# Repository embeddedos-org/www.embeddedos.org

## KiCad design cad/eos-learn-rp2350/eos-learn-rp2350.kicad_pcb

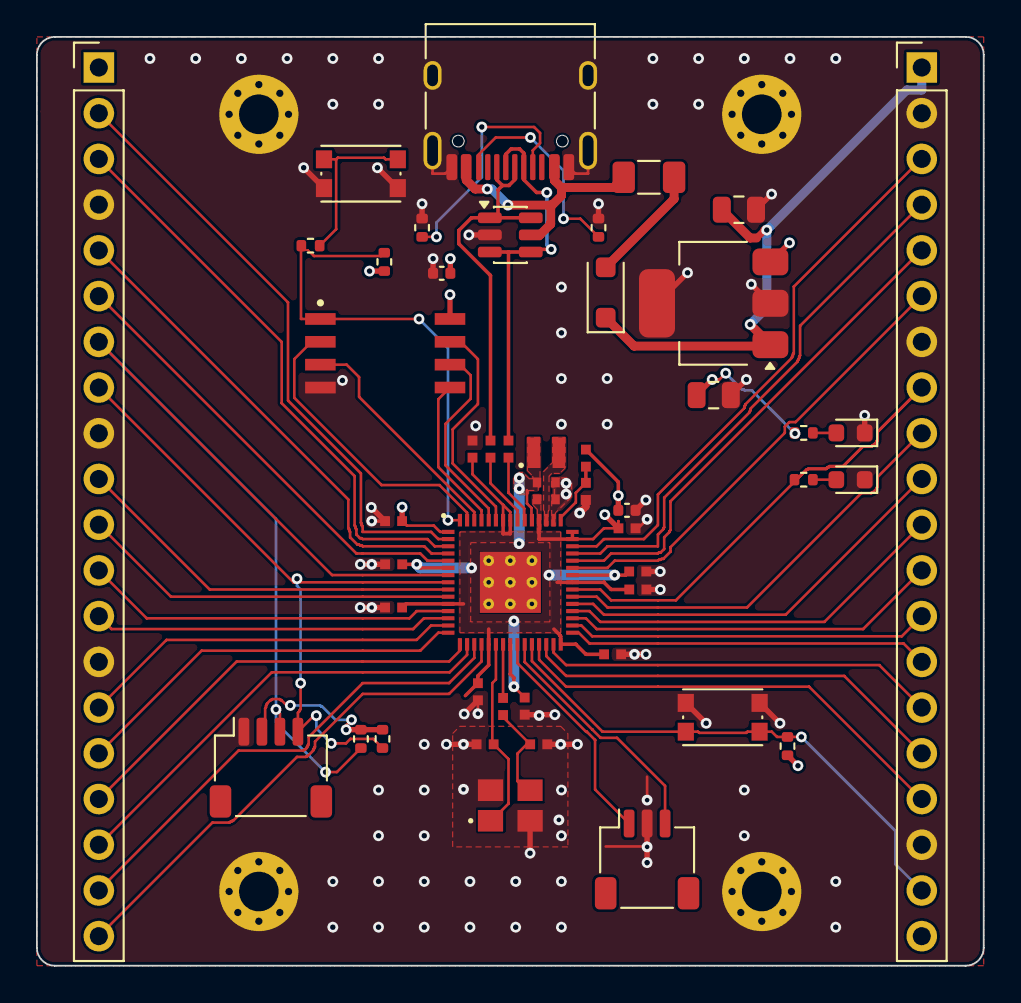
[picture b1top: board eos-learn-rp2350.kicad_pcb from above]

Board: 4 copper layers, 52.6 x 51.6 mm, 53 parts (0 on the bottom side), 59 nets.

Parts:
C1, C2: 10u; C_0805_2012Metric
C3, C4: 15p; generic_capc1005x50
C6, C7: 4.7u; generic_capc1005x50_wide
C9: 4.7u; generic_capc1005x50
C10, C11, C12, C13, C14, C15, C16, C18, C19, C20: 100n; generic_capc1005x50
C17, C21: 100n; C_0402_1005Metric
D1: MBR120VLSFT1G; D_SOD-123F
D2: PWR; LED_0603_1608Metric
D3: GP25; LED_0603_1608Metric
F1: 500mA; Fuse_1206_3216Metric
H1, H2, H3, H4: M2; MountingHole_2.2mm_M2_Pad_Via
J1: USB-C; USB_C_Receptacle_HRO_TYPE-C-31-M-12
J2: GPIO 0-15; PinHeader_1x20_P2.54mm_Vertical
J3: Power, GPIO 16-29; PinHeader_1x20_P2.54mm_Vertical
J4: SWD; JST_SH_SM03B-SRSS-TB_1x03-1MP_P1.00mm_Horizontal
J5: Qwiic; JST_SH_SM04B-SRSS-TB_1x04-1MP_P1.00mm_Horizontal
L1: 3.3u; abracon_aota-b201610s3r3-101-t
R1, R2: 5.1k; R_0402_1005Metric
R3, R4: 27; generic_resc1005x35
R5, R8: 1k; R_0402_1005Metric
R6: 33; generic_resc1005x35
R7, R9: 10k; R_0402_1005Metric
R10: 1k; generic_resc1005x35
R11: 470; R_0402_1005Metric
R12, R13: 4.7k; R_0402_1005Metric
SW1: BOOTSEL; SW_Push_1P1T_NO_CK_KMR2
SW2: RUN; SW_Push_1P1T_NO_CK_KMR2
U1: RP2350A; rpi_rp2350a_vias
U2: USBLC6-2SC6; SOT-23-6
U3: AP7361C-33; SOT-223-3_TabPin2
U4: W25Q128JVS; generic_soic127p790x195-8
Y1: 12MHz; generic_xtalcc320x250x80-4

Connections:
+1V1: C7.1, C18.1, C19.1, C20.1, L1.1, U1.6 (DVDD), U1.23 (DVDD), U1.39 (DVDD), U1.50 (VREG_FB)
+3V3: C2.1, C6.1, C10.1, C11.1, C12.1, C13.1, C14.1, C15.1, C16.1, C17.1, C21.1, J2.1, J3.20, J5.2, R5.1, R6.1, R7.2, R9.2, R12.2, R13.2, U1.1 (IOVDD), U1.11 (IOVDD), U1.20 (IOVDD), U1.30 (IOVDD), U1.38 (IOVDD), U1.44 (ADC_AVDD), U1.45 (IOVDD), U1.49 (VREG_VIN), U1.53 (USB_OTP_VDD), U1.54 (QSPI_IOVDD), U3.3, U4.8 (VCC)
+5V: C1.1, D1.1, J3.1, U3.1
/BOOTSEL: R8.2, SW1.1
/CC1: J1.A5, R1.1
/CC2: J1.B5, R2.1
/GPIO0: J2.2, U1.2 (GPIO0)
/GPIO1: J2.3, U1.3 (GPIO1)
/GPIO2: J2.5, U1.4 (GPIO2)
/GPIO3: J2.6, U1.5 (GPIO3)
/GPIO4: J2.7, J5.3, R12.1, U1.7 (GPIO4)
/GPIO5: J2.8, J5.4, R13.1, U1.8 (GPIO5)
/GPIO6: J2.10, U1.9 (GPIO6)
/GPIO7: J2.11, U1.10 (GPIO7)
/GPIO8: J2.12, U1.12 (GPIO8)
/GPIO9: J2.13, U1.13 (GPIO9)
/GPIO10: J2.15, U1.14 (GPIO10)
/GPIO11: J2.16, U1.15 (GPIO11)
/GPIO12: J2.17, U1.16 (GPIO12)
/GPIO13: J2.18, U1.17 (GPIO13)
/GPIO14: J2.19, U1.18 (GPIO14)
/GPIO15: J2.20, U1.19 (GPIO15)
/GPIO16: J3.17, U1.27 (GPIO16)
/GPIO17: J3.16, U1.28 (GPIO17)
/GPIO18: J3.15, U1.29 (GPIO18)
/GPIO19: J3.14, U1.31 (GPIO19)
/GPIO20: J3.13, U1.32 (GPIO20)
/GPIO21: J3.12, U1.33 (GPIO21)
/GPIO22: J3.11, U1.34 (GPIO22)
/GPIO23: J3.10, U1.35 (GPIO23)
/GPIO24: J3.9, U1.36 (GPIO24)
/GPIO25: J3.8, R11.1, U1.37 (GPIO25)
/GPIO26_ADC0: J3.6, U1.40 (GPIO26_ADC0)
/GPIO27_ADC1: J3.5, U1.41 (GPIO27_ADC1)
/GPIO28_ADC2: J3.4, U1.42 (GPIO28_ADC2)
/GPIO29_ADC3: J3.3, U1.43 (GPIO29_ADC3)
/LED_PWR_A: D2.2, R5.2
/LED_USR_A: D3.2, R11.2
/QSPI_SCLK: U1.56 (QSPI_SCLK), U4.6 (CLK)
/QSPI_SD0: U1.57 (QSPI_SD0), U4.5 (DI_IO0)
/QSPI_SD1: U1.59 (QSPI_SD1), U4.2 (DO_IO1)
/QSPI_SD2: U1.58 (QSPI_SD2), U4.3 (~WP_IO2)
/QSPI_SD3: U1.55 (QSPI_SD3), U4.7 (~HOLD_IO3)
/QSPI_SS: R7.1, R8.1, U1.60 (QSPI_~SS), U4.1 (~CS)
/RP_USB_DM: R4.2, U1.51 (USB_DM)
/RP_USB_DP: R3.2, U1.52 (USB_DP)
/RUN: J3.19, R9.1, SW2.1, U1.26 (RUN)
/SWCLK: J4.1, U1.24 (SWCLK)
/SWDIO: J4.3, U1.25 (SWDIO)
/USB_D+: J1.A6, J1.B6, R3.1, U2.1, U2.6
/USB_D-: J1.A7, J1.B7, R4.1, U2.3, U2.4
/VBUS_F: D1.2, F1.2
/VREG_AVDD: C9.1, R6.2, U1.46 (VREG_AVDD)
/VREG_LX: L1.2, U1.48 (VREG_LX)
/XIN: C3.1, U1.21 (XIN), Y1.1
/XOUT: R10.1, U1.22 (XOUT)
/XTAL_OUT: C4.1, R10.2, Y1.3
GND: C1.2, C2.2, C3.2, C4.2, C6.2, C7.2, C9.2, C10.2, C11.2, C12.2, C13.2, C14.2, C15.2, C16.2, C17.2, C18.2, C19.2, C20.2, C21.2, D2.1, D3.1, H1.1, H2.1, H3.1, H4.1, J1.A1, J1.A12, J1.B1, J1.B12, J1.SH, J2.4, J2.9, J2.14, J3.2, J3.7, J3.18, J4.2, J5.1, R1.2, R2.2, SW1.2, SW2.2, U1.47 (VREG_PGND), U1.61 (GND), U2.2, U3.2, U4.4 (GND), Y1.2, Y1.4
VBUS: F1.1, J1.A4, J1.A9, J1.B4, J1.B9, U2.5

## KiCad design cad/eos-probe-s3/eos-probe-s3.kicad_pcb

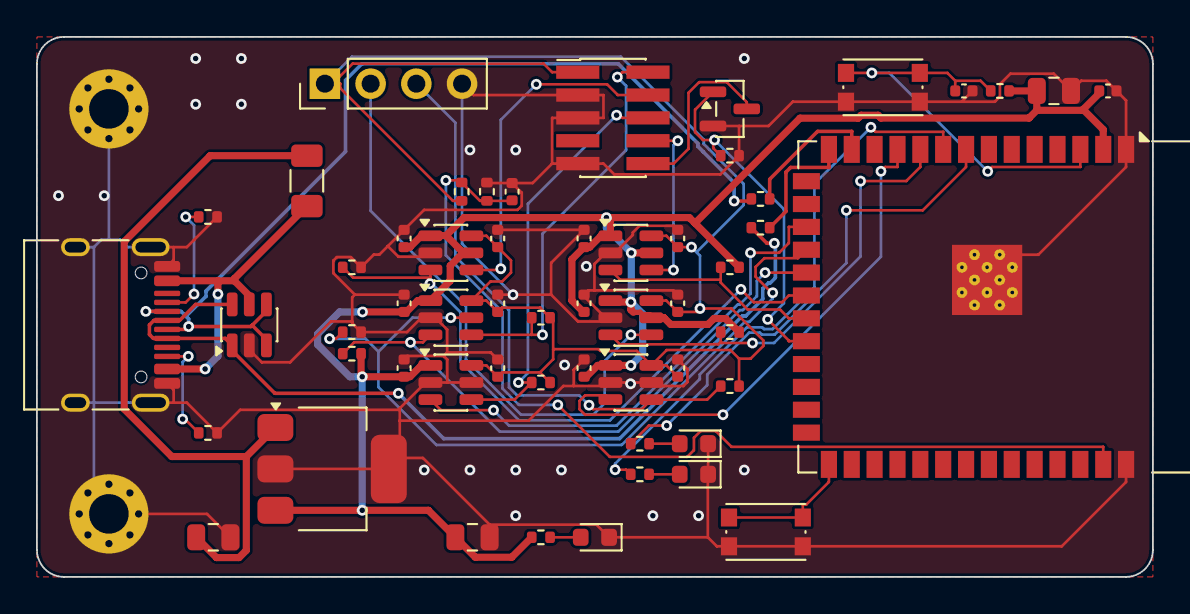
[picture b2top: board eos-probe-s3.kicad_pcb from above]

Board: 2 copper layers, 62.0 x 30.0 mm, 58 parts (0 on the bottom side), 34 nets.

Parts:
C1, C2: 4.7u; C_0805_2012Metric
C3: 22u; C_0805_2012Metric
C4, C6, C7, C8, C9, C10, C11, C12, C13, C14, C15, C16, C17, C18: 100n; C_0402_1005Metric
C5: 1u; C_0402_1005Metric
D1: PWR; LED_0603_1608Metric
D2: STAT; LED_0603_1608Metric
D3: ACT; LED_0603_1608Metric
F1: 500mA; Fuse_1206_3216Metric
H1, H2: M2; MountingHole_2.2mm_M2_Pad_Via
J1: USB-C; USB_C_Receptacle_HRO_TYPE-C-31-M-12
J2: Cortex Debug; PinHeader_2x05_P1.27mm_Vertical_SMD
J3: Target UART; PinHeader_1x04_P2.54mm_Vertical
Q1: 2N7002; SOT-23
R1, R2: 5.1k; R_0402_1005Metric
R3: 1k; R_0402_1005Metric
R4: 10k; R_0402_1005Metric
R5, R6: 0; R_0402_1005Metric
R7, R8: 470; R_0402_1005Metric
R9, R10, R11, R12, R13, R14, R15, R16, R17, R18, R19: 100k; R_0402_1005Metric
SW1: RESET; SW_Push_1P1T_NO_CK_KMR2
SW2: BOOT; SW_Push_1P1T_NO_CK_KMR2
U1: USBLC6-2SC6; SOT-23-6
U2: AP7361C-33; SOT-223-3_TabPin2
U3: ESP32-S3-WROOM-1-N8R2; ESP32-S3-WROOM-1
U4, U5, U6, U7, U8, U9: SN74LVC1T45; SOT-23-6

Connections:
+3V3: C2.1, C3.1, C4.1, C6.1, C7.1, C8.1, C9.1, C10.1, C11.1, R3.1, R4.2, R11.2, R12.2, R13.2, U2.3, U3.2, U4.1, U4.5, U5.1, U6.1, U7.1, U7.5, U8.1, U8.5, U9.1
+5V: C1.1, F1.2, U2.1
/BOOT: SW2.1, U3.27
/CC1: J1.A5, R1.1
/CC2: J1.B5, R2.1
/EN: C5.1, R4.1, SW1.1, U3.3
/ESP_D+: R6.2, U3.14
/ESP_D-: R5.2, U3.13
/LED_ACT: R8.1, U3.9
/LED_ACT_A: D3.2, R8.2
/LED_PWR_A: D1.2, R3.2
/LED_STAT: R7.1, U3.8
/LED_STAT_A: D2.2, R7.2
/NRESET_G: Q1.1, R17.1, U3.22
/SWCLK_A: R9.1, U3.20, U4.3
/SWDIO_A: R11.1, U3.19, U5.3
/SWDIO_DIR: R10.1, U3.18, U5.5
/SWO_A: U3.17, U6.3
/TDI_A: R12.1, U3.21, U7.3
/T_NRESET: J2.10, Q1.3
/T_SWCLK: J2.4, U4.4
/T_SWDIO: J2.2, R14.1, U5.4
/T_SWO: J2.6, R15.1, U6.4
/T_TDI: J2.8, U7.4
/T_UART_RX: J3.3, R16.1, U9.4
/T_UART_TX: J3.2, U8.4
/UART_RX_A: U3.11, U9.3
/UART_TX_A: R13.1, U3.10, U8.3
/USB_D+: J1.A6, J1.B6, R6.1, U1.1, U1.6
/USB_D-: J1.A7, J1.B7, R5.1, U1.3, U1.4
/VTREF: C12.1, C13.1, C14.1, C15.1, C16.1, C17.1, J2.1, J3.1, R14.2, R15.2, R16.2, R18.1, U4.6, U5.6, U6.6, U7.6, U8.6, U9.6
/VTREF_SENSE: C18.1, R18.2, R19.1, U3.39
GND: C1.2, C2.2, C3.2, C4.2, C5.2, C6.2, C7.2, C8.2, C9.2, C10.2, C11.2, C12.2, C13.2, C14.2, C15.2, C16.2, C17.2, C18.2, D1.1, D2.1, D3.1, H1.1, H2.1, J1.A1, J1.A12, J1.B1, J1.B12, J1.SH, J2.3, J2.5, J2.9, J3.4, Q1.2, R1.2, R2.2, R9.2, R10.2, R17.2, R19.2, SW1.2, SW2.2, U1.2, U2.2, U3.1, U3.40, U3.41, U4.2, U5.2, U6.2, U6.5, U7.2, U8.2, U9.2, U9.5
VBUS: F1.1, J1.A4, J1.A9, J1.B4, J1.B9, U1.5

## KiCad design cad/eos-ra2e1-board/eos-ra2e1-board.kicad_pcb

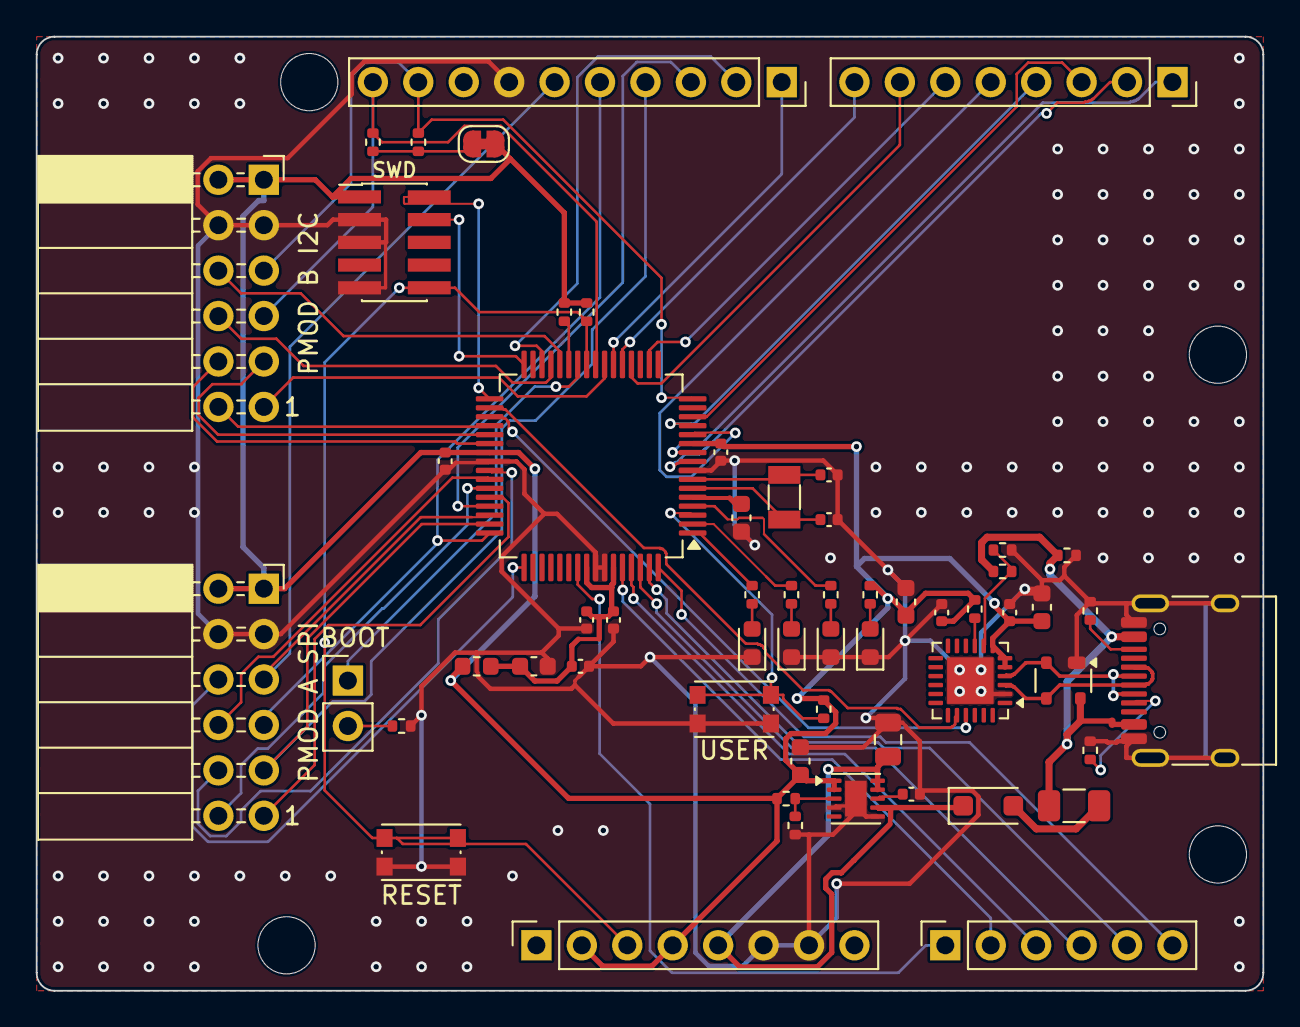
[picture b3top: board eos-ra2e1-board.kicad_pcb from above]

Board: 2 copper layers, 68.6 x 53.3 mm, 62 parts (1 on the bottom side), 67 nets.

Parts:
C1, C2, C6, C7, C17, C19: 100n; C_0402_1005Metric
C3, C16, C18: 4.7u; C_0603_1608Metric
C4: 18p; C_0402_1005Metric
C5: 15p; C_0402_1005Metric
C8, C14: 10u; C_0603_1608Metric
C9, C15: 10n; C_0402_1005Metric
C13: 10u; C_0805_2012Metric
D1: PMEG6010CEH; D_SOD-123F
D2: PWR; LED_0603_1608Metric
D3: LED1; LED_0603_1608Metric
D4: LED2; LED_0603_1608Metric
D5: LED3; LED_0603_1608Metric
F1: 500mA; Fuse_1206_3216Metric
FB1: 220R; L_0603_1608Metric
H1, H2, H3, H4: M3; MountingHole_3.2mm_M3_ISO14580
J1: USB-C; USB_C_Receptacle_HRO_TYPE-C-31-M-12
J2: SWD; PinHeader_2x05_P1.27mm_Vertical_SMD
J3: D8-SCL; PinSocket_1x10_P2.54mm_Vertical
J4: D0-D7; PinSocket_1x08_P2.54mm_Vertical
J5: POWER; PinSocket_1x08_P2.54mm_Vertical
J6: A0-A5; PinSocket_1x06_P2.54mm_Vertical
J7: PMOD A; PinSocket_2x06_P2.54mm_Horizontal
J8: PMOD B; PinSocket_2x06_P2.54mm_Horizontal
JP1: MD; PinHeader_1x02_P2.54mm_Vertical
JP2: I2C PU; SolderJumper-2_P1.3mm_Bridged_RoundedPad1.0x1.5mm
R1, R2: 5.1k; R_0402_1005Metric
R3, R4: 2.2k; R_0402_1005Metric
R5: 22.1k; R_0402_1005Metric
R6: 47.5k; R_0402_1005Metric
R7, R14: 1.5k; R_0402_1005Metric
R8: 3.57k; R_0402_1005Metric
R9: 1.15k; R_0402_1005Metric
R10, R17, R18: 680; R_0402_1005Metric
R11: 1k; R_0402_1005Metric
R12, R13, R15: 10k; R_0402_1005Metric
R16: 750; R_0402_1005Metric
SW1: RESET; SW_Push_1P1T_NO_CK_KMR2
SW2: USER; SW_Push_1P1T_NO_CK_KMR2
U1: R7FA2E1A92DFM; LQFP-64_10x10mm_P0.5mm
U2: SP0503BAHTG; SOT-143
U3: CP2102N-A02-GQFN24; QFN-24-1EP_4x4mm_P0.5mm_EP2.6x2.6mm
U4: TPS7A91; Texas_S-PDSO-N10_EP1.2x2mm
Y1: 32.768kHz; Crystal_SMD_3215-2Pin_3.2x1.5mm

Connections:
+3V3: C1.1, C2.1, C14.1, C16.1, C17.1, C18.1, C19.1, FB1.1, J2.1, J5.2, J5.4, J7.1, J7.2, J8.1, J8.2, JP2.2, R8.1, R10.2, R11.2, R12.2, R13.2, R15.2, U1.11, U1.39, U3.5, U3.6, U3.7, U4.1, U4.2
+5V: C13.1, D1.1, J5.5, U4.7, U4.9, U4.10
/A0: J6.1, U1.55
/A1: J6.2, U1.60
/A2: J6.3, U1.61
/A3: J6.4, U1.62
/A4: J6.5, U1.63
/A5: J6.6, U1.64
/AVCC0: C6.1, C7.1, C8.1, C9.1, FB1.2, U1.56, U1.59
/CC1: J1.A5, R1.1
/CC2: J1.B5, R2.1
/CP_RST: R11.1, U3.9
/CP_VBUS: R5.2, R6.1, U3.8
/D0: J4.1, U1.10
/D1: J4.2, U1.9
/D2: J4.3, U1.14
/D3: J4.4, U1.13
/D4: J4.5, U1.12
/D5: J4.6, U1.18
/D6: J4.7, U1.20
/D7: J4.8, U1.21
/D8: J3.1, U1.22
/D9: J3.2, U1.30
/D10: J3.3, U1.45
/I2C_PU: JP2.1, R3.1, R4.1
/LDO_FB: R8.2, R9.1, U4.3
/LDO_NR: C15.1, U4.8
/LED1: R16.2, U1.1
/LED1_A: D3.2, R16.1
/LED2: R17.2, U1.2
/LED2_A: D4.2, R17.1
/LED3: R18.2, U1.4
/LED3_A: D5.2, R18.1
/LED_PWR_A: D2.2, R10.1
/MD: JP1.1, U1.26
/MD_JP: JP1.2, R14.1
/NMI: R13.1, U1.27
/PMODA_CS: J7.11, U1.44
/PMODA_CS2: J7.8, U1.42
/PMODA_CS3: J7.6, U1.49
/PMODA_INT: J7.12, U1.43
/PMODA_RST: J7.10, U1.41
/PMODB_INT: J8.11, U1.23
/PMODB_IO7: J8.12, U1.36
/PMODB_IO8: J8.10, U1.38
/PMODB_IO9: J8.8, U1.29
/PMODB_IO10: J8.6, U1.28
/PMODB_RST: J8.9, U1.37
/RES: J2.10, J5.3, R12.1, SW1.1, U1.25
/RXD9: U1.35, U3.21
/SCL: J3.10, J8.7, R3.2, U1.24
/SDA: J3.9, J8.5, R4.2, U1.16
/SPI_MISO: J3.5, J7.7, U1.48
/SPI_MOSI: J3.4, J7.9, U1.47
/SPI_SCK: J3.6, J7.5, U1.46
/SWCLK: J2.4, U1.32
/SWDIO: J2.2, U1.33
/TXD9: U1.34, U3.20
/USB_DM: J1.A7, J1.B7, U2.2, U3.4
/USB_DP: J1.A6, J1.B6, U2.3, U3.3
/USER_BTN: R15.1, SW2.1, U1.3
/VBUS: F1.1, J1.A4, J1.A9, J1.B4, J1.B9, R5.1, R7.1, U2.4
/VBUS_F: D1.2, F1.2
/VCL: C3.1, U1.5
/XCIN: C5.1, U1.6, Y1.2
/XCOUT: C4.1, U1.7, Y1.1
GND: C1.2, C2.2, C3.2, C4.2, C5.2, C6.2, C7.2, C8.2, C9.2, C13.2, C14.2, C15.2, C16.2, C17.2, C18.2, C19.2, D2.1, D3.1, D4.1, D5.1, J1.A1, J1.A12, J1.B1, J1.B12, J1.SH, J2.3, J2.5, J2.9, J3.7, J5.6, J5.7, J7.3, J7.4, J8.3, J8.4, R1.2, R2.2, R6.2, R7.2, R9.2, R14.2, SW1.2, SW2.2, U1.8, U1.40, U1.57, U1.58, U2.1, U3.2, U3.25, U4.4, U4.6, U4.11

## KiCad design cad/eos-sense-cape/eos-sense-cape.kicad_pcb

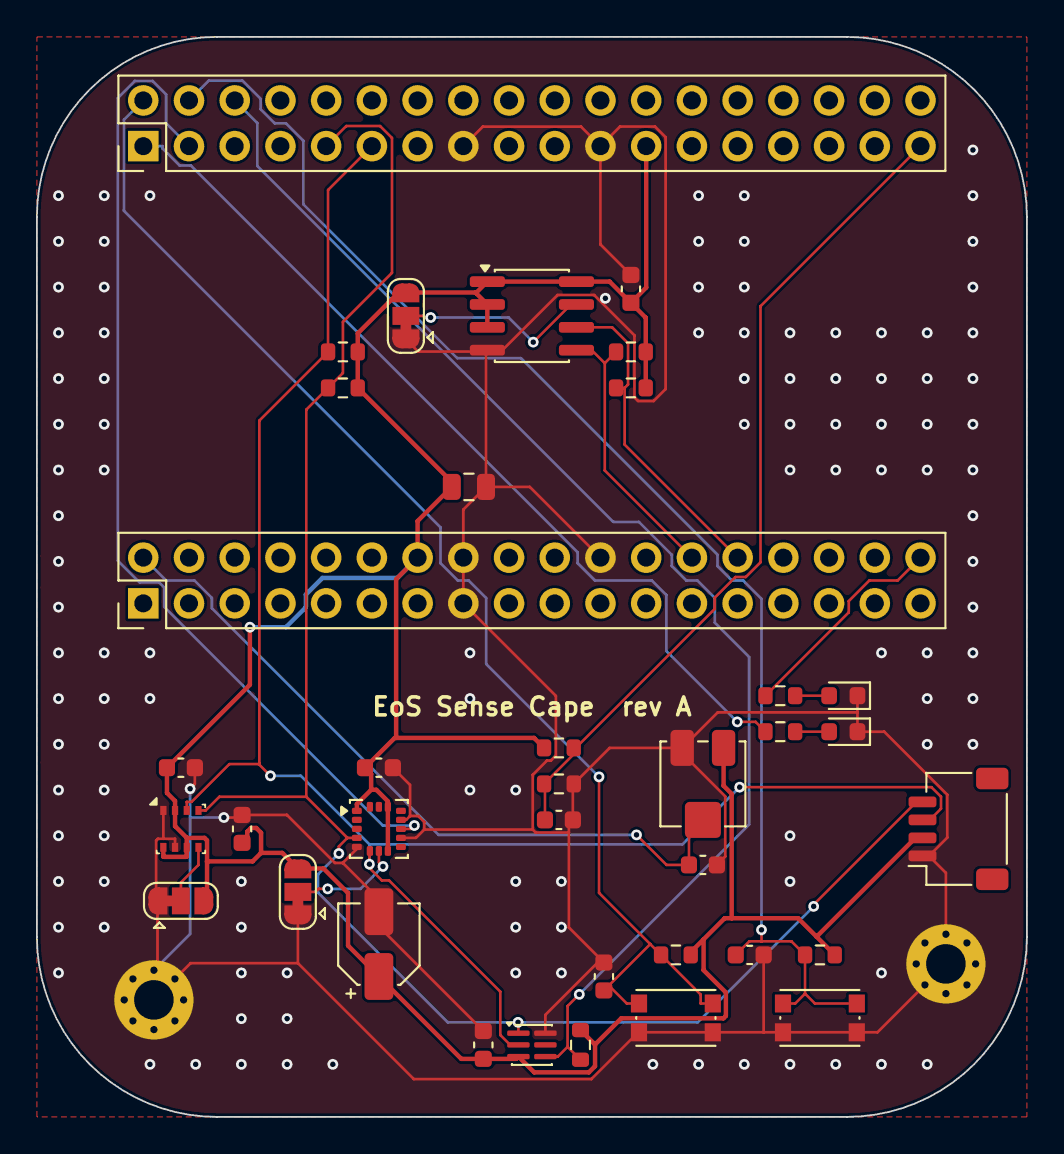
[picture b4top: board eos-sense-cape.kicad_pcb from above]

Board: 2 copper layers, 55.0 x 60.0 mm, 39 parts (0 on the bottom side), 19 nets.

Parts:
C1: 10u; C_0805_2012Metric
C2, C3, C4, C7, C8, C9, C10, C11: 100n; C_0603_1608Metric
C5: 10u; CP_Elec_4x5.4
C6: 1u; C_0603_1608Metric
D1: RED; LED_0603_1608Metric
D2: YEL; LED_0603_1608Metric
H1, H2: M2; MountingHole_2.2mm_M2_Pad_Via
J1: PocketBeagle P1; PinHeader_2x18_P2.54mm_Vertical
J2: PocketBeagle P2; PinHeader_2x18_P2.54mm_Vertical
J3: Qwiic; JST_SH_SM04B-SRSS-TB_1x04-1MP_P1.00mm_Horizontal
JP1: WP; SolderJumper-3_P1.3mm_Bridged12_RoundedPad1.0x1.5mm
JP2: 0x76; SolderJumper-3_P1.3mm_Bridged12_RoundedPad1.0x1.5mm
JP3: 0x18; SolderJumper-3_P1.3mm_Bridged12_RoundedPad1.0x1.5mm
R1, R2, R4, R5: 4.7k; R_0603_1608Metric
R3, R6, R7, R8: 10k; R_0603_1608Metric
R9, R10: 680; R_0603_1608Metric
RV1: 10k; Potentiometer_Bourns_3314J_Vertical
SW1: BTN1; SW_Push_1P1T_NO_CK_KMR2
SW2: BTN2; SW_Push_1P1T_NO_CK_KMR2
TH1: 10k; R_0603_1608Metric
U1: BME280; Bosch_LGA-8_2.5x2.5mm_P0.65mm_ClockwisePinNumbering
U2: LIS3DH; LGA-16_3x3mm_P0.5mm_LayoutBorder3x5y
U3: APDS-9306-065; Broadcom_DFN-6_2x2mm_P0.65mm
U4: 24LC256; SOIC-8_3.9x4.9mm_P1.27mm

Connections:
+3V3: C1.1, C2.1, C3.1, C4.1, C5.1, C6.1, C7.1, J1.14, J2.23, J3.2, JP1.3, JP2.3, JP3.3, R1.2, R2.2, R3.2, R4.2, R5.2, R6.1, R7.2, R8.2, RV1.1, U1.2, U1.6, U1.8, U2.1, U2.8, U2.14, U3.3, U4.1, U4.2, U4.3, U4.8
/ACC_INT1: J2.3, U2.11
/ACC_SA0: JP3.2, U2.7
/AIN5: C8.1, J2.35, R6.2, TH1.1
/AIN6: C9.1, J1.2, RV1.2
/ALS_INT: J2.6, R3.1, U3.4
/BME_SDO: JP2.2, U1.5
/BTN1: C10.1, J2.2, R7.1, SW1.1
/BTN2: C11.1, J2.4, R8.1, SW2.1
/EE_WP: JP1.2, U4.7
/I2C1_SCL: J2.9, J3.4, R2.1, U1.4, U2.4, U3.1
/I2C1_SDA: J2.11, J3.3, R1.1, U1.3, U2.6, U3.2
/I2C2_SCL: J1.28, R5.1, U4.6
/I2C2_SDA: J1.26, R4.1, U4.5
/LED1: J1.36, R9.1
/LED1_A: D1.2, R9.2
/LED2: J2.1, R10.1
/LED2_A: D2.2, R10.2
GND: C1.2, C2.2, C3.2, C4.2, C5.2, C6.2, C7.2, C8.2, C9.2, C10.2, C11.2, D1.1, D2.1, H1.1, H2.1, J1.15, J1.16, J1.22, J2.15, J2.21, J3.1, JP1.1, JP2.1, JP3.1, RV1.3, SW1.2, SW2.2, TH1.2, U1.1, U1.7, U2.5, U2.10, U2.12, U3.6, U4.4

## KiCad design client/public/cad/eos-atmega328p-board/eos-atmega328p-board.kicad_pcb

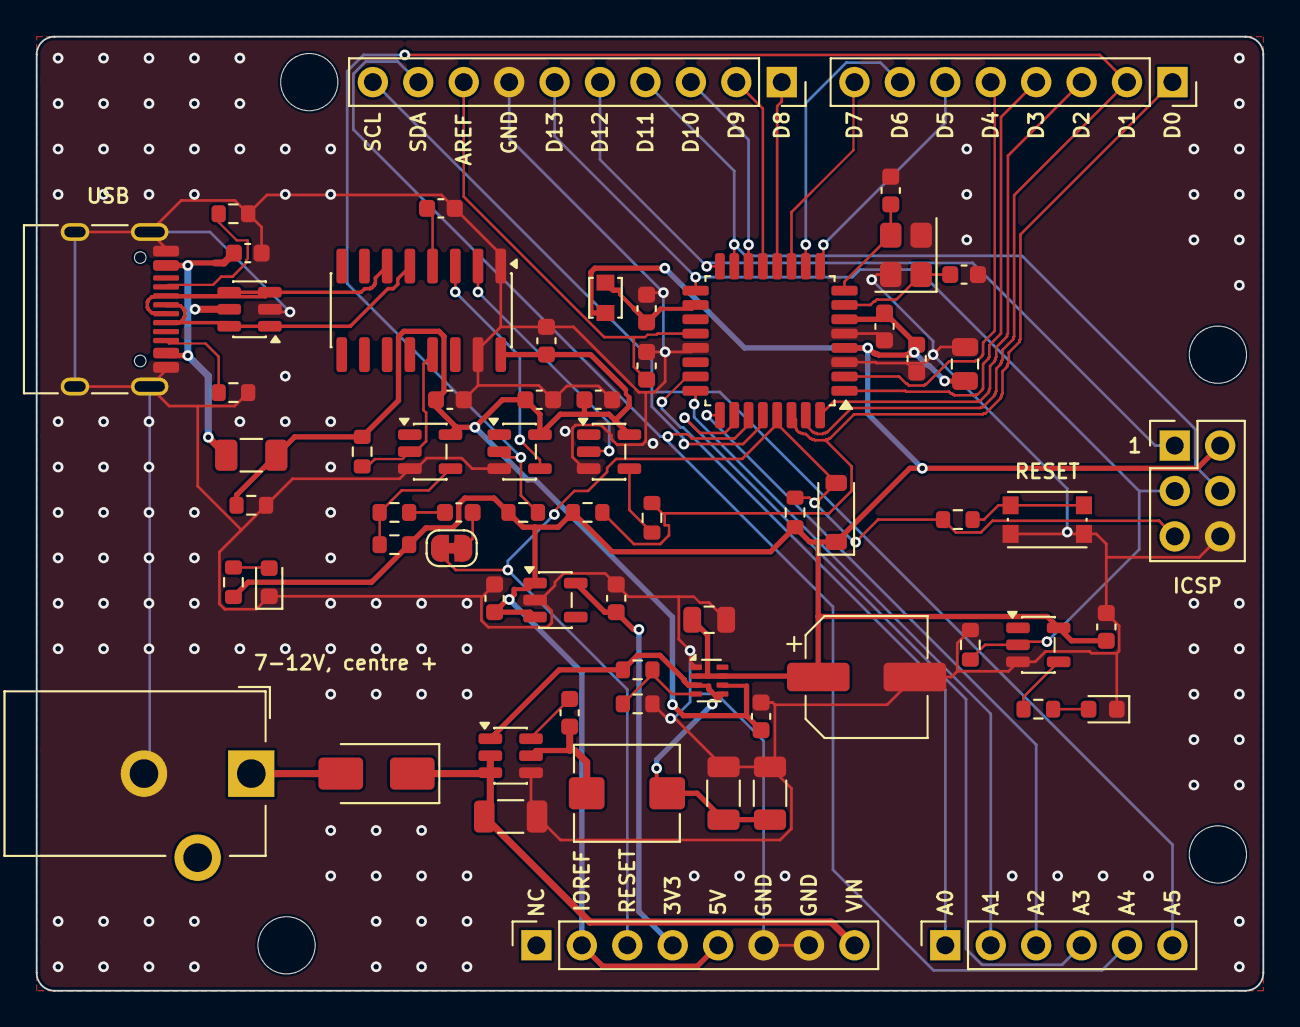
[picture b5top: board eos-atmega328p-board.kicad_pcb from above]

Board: 2 copper layers, 68.6 x 53.3 mm, 71 parts (1 on the bottom side), 52 nets.

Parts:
C1: 10u; C_1206_3216Metric
C2, C9, C10, C11, C12, C13, C15, C16, C19, C21, C22, C23, C24: 100n; C_0603_1608Metric
C3, C4: 22u; C_1206_3216Metric
C5, C7, C8: 1u; C_0603_1608Metric
C6: 100u; CP_Elec_6.3x5.8
C14, C20: 10u; C_0805_2012Metric
C17, C18: 18p; C_0603_1608Metric
D1: B240A; D_SMA
D2: PWR; LED_0603_1608Metric
D3: 1N4148W; D_SOD-123
D4: L; LED_0603_1608Metric
F1: 500mA; Fuse_1206_3216Metric
H1, H2, H3, H4: M3; MountingHole_3.2mm_M3_ISO14580
J1: USB-C; USB_C_Receptacle_HRO_TYPE-C-31-M-12
J2: 7-12V; BarrelJack_CUI_PJ-102AH_Horizontal
J3: D0-D7; PinSocket_1x08_P2.54mm_Vertical
J4: D8-SCL; PinSocket_1x10_P2.54mm_Vertical
J5: POWER; PinSocket_1x08_P2.54mm_Vertical
J6: A0-A5; PinSocket_1x06_P2.54mm_Vertical
J7: ICSP; PinHeader_2x03_P2.54mm_Vertical
JP1: AUTO-RST; SolderJumper-2_P1.3mm_Bridged_RoundedPad1.0x1.5mm
L1: 4.7u; L_Bourns_SRP5030T
L2: 10u; L_Murata_LQH2MCNxxxx02_2.0x1.6mm
R1, R2: 5.1k; R_0603_1608Metric
R3: 33k; R_0603_1608Metric
R4, R8, R13, R14, R15: 10k; R_0603_1608Metric
R5, R11: 1.5k; R_0603_1608Metric
R6: 1k; R_0603_1608Metric
R7, R10, R16: 100k; R_0603_1608Metric
R9: 330; R_0603_1608Metric
R12: 220; R_0603_1608Metric
SW1: RESET; SW_Push_1P1T_NO_CK_KMR2
U1: USBLC6-2SC6; SOT-23-6
U2: AP63205; TSOT-23-6
U3: TPS2116; SOT-583-8
U4: AP2112K-3.3; SOT-23-5
U5: CH340C; SOIC-16_3.9x9.9mm_P1.27mm
U6: ATmega328P-AU; TQFP-32_7x7mm_P0.8mm
U7, U8, U9: SN74LVC1G17; SOT-23-5
U10: SN74LVC1G07; SOT-23-5
Y1: 16MHz; Crystal_SMD_3225-4Pin_3.2x2.5mm

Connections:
+3V3: C8.1, J5.4, U4.5
+5V: C6.1, C7.1, C12.1, C13.1, C14.1, C19.1, C20.1, D3.1, J5.2, J5.5, J7.2, L2.1, R5.1, R7.1, R8.1, R13.1, R15.2, U3.2, U3.7, U4.1, U4.3, U6.4, U6.6, U7.5
/5V_REG: C3.1, C4.1, L1.2, R3.1, U2.1, U3.3, U3.5
/A0: J6.1, U6.23
/A1: J6.2, U6.24
/A2: J6.3, U6.25
/A3: J6.4, U6.26
/A4_SDA: J4.9, J6.5, U6.27
/A5_SCL: J4.10, J6.6, U6.28
/AREF: C16.1, J4.8, U6.20
/AVCC: C15.1, L2.2, U6.18
/BUCK_BST: C2.2, U2.6
/BUCK_SW: C2.1, L1.1, U2.5
/CC1: J1.A5, R1.1
/CC2: J1.B5, R2.1
/CH_DTR: R16.1, U5.13, U10.2
/CH_RX: U5.3, U8.4
/CH_TX: U5.2, U9.2
/CH_V3: C10.1, U5.4
/D0: J3.1, R6.2, R13.2, U6.30
/D0_BUF: R6.1, U9.4
/D1: J3.2, R7.2, U6.31, U8.2
/D2: J3.3, U6.32
/D3: J3.4, U6.1
/D4: J3.5, U6.2
/D5: J3.6, U6.9
/D6: J3.7, U6.10
/D7: J3.8, U6.11
/D8: J4.1, U6.12
/D9: J4.2, U6.13
/D10: J4.3, U6.14
/D11: J4.4, J7.4, U6.15
/D12: J4.5, J7.1, U6.16
/D13: J4.6, J7.3, R10.1, U6.17, U7.2
/DTR_BUF: R12.1, R15.1, U10.4
/DTR_C: C11.1, R12.2
/DTR_JP: C11.2, JP1.1
/LED_L_A: D4.2, R11.2
/LED_L_DRV: R11.1, U7.4
/LED_PWR_A: D2.2, R5.2
/MUX_PR1: R3.2, R4.1, U3.4
/RESET: D3.2, J5.3, J7.5, JP1.2, R8.2, R9.1, U6.29
/RST_SW: R9.2, SW1.1
/USB_D+: J1.A6, J1.B6, U1.1, U1.6, U5.5
/USB_D-: J1.A7, J1.B7, U1.3, U1.4, U5.6
/VIN: C1.1, D1.1, J5.8, U2.2, U2.3
/VJACK: D1.2, J2.1
/VUSB: C5.1, C9.1, C22.1, C23.1, C24.1, F1.2, R14.1, R16.2, U3.6, U5.16, U8.5, U9.5, U10.5
/XTAL1: C17.1, U6.7, Y1.1
/XTAL2: C18.1, U6.8, Y1.3
GND: C1.2, C3.2, C4.2, C5.2, C6.2, C7.2, C8.2, C9.2, C10.2, C12.2, C13.2, C14.2, C15.2, C16.2, C17.2, C18.2, C19.2, C20.2, C21.2, C22.2, C23.2, C24.2, D2.1, D4.1, J1.A1, J1.A12, J1.B1, J1.B12, J1.SH, J2.2, J4.7, J5.6, J5.7, J7.6, R1.2, R2.2, R4.2, R10.2, R14.2, SW1.2, U1.2, U2.4, U3.1, U4.2, U5.1, U5.15, U6.3, U6.5, U6.21, U7.3, U8.3, U9.3, U10.3, Y1.2, Y1.4
VBUS: C21.1, F1.1, J1.A4, J1.A9, J1.B4, J1.B9, U1.5

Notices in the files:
cad/eos-learn-rp2350/eos-learn-rp2350.kicad_pcb:
Core layout (c) 2026 Raspberry Pi Ltd  MIT
client/public/cad/eos-ke16z-board/eos-ke16z-board.kicad_sch:
Copyright (c) 2026 Kartikeydheer Srivastava. Licence: All rights reserved
Uno R3 header and hole positions cross-checked against KiCad 10's Module:Arduino_UNO_R3_WithMountingHoles footprint (KiCad libraries, CC BY-SA 4.0); positions only, the footprint is not used
